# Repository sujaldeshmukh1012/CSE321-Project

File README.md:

<div id="top">

<!-- HEADER STYLE: CLASSIC -->
<div align="center">

# GuardianHAT

<em>Real-Time Embedded System for GPS Tracking and Environmental Monitoring</em>

<!-- BADGES -->

<em>Built with the tools and technologies:</em>

**C/C++ • ESP32-CAM • Arduino Nano • FreeRTOS • PlatformIO • KiCad PCB Design**

</div>
<br>

---

## Table of Contents

- [Overview](#overview)
- [Features](#features)
- [Hardware Components](#hardware-components)
- [PCB Design](#pcb-design)
  - [PCB Images](#pcb-images)
  - [Design Process](#design-process)
  - [Bill of Materials](#bill-of-materials)
- [Project Structure](#project-structure)
- [Getting Started](#getting-started)
  - [Prerequisites](#prerequisites)
  - [Installation](#installation)
  - [Usage](#usage)
  - [Testing](#testing)
- [System Architecture](#system-architecture)
- [Implimentation](#implimentation)
- [Contributing](#contributing)
- [License](#license)
- [Author](#author)
- [Acknowledgments](#acknowledgments)

---

## Overview

GuardianHAT is a comprehensive embedded systems solution that integrates GPS tracking, environmental sensing, and real-time monitoring capabilities. The project features two main components: an ESP32-CAM based system for camera functionality and location tracking, and an Arduino Nano RTOS implementation for sensor data processing with FreeRTOS task management.

The system includes a custom-designed PCB (Caretaker Board) that integrates all components for a professional, production-ready embedded solution.

**Key Highlights:**
- Real-time GPS satellite tracking and location monitoring
- Environmental sensing with MPU6050 (accelerometer/gyroscope)
- Distance measurement using VL53L0X ToF sensor
- OLED display (SSD1306) for real-time data visualization
- Custom PCB design with professional manufacturing files
- Multi-threaded RTOS implementation for concurrent task execution

---

## Features

### Core Functionality
- **GPS Tracking**: Real-time satellite position tracking with TinyGPS++ library
- **Motion Detection**: 6-axis motion sensing using MPU6050 (accelerometer + gyroscope)
- **Distance Measurement**: Precise ranging with VL53L0X Time-of-Flight sensor
- **Visual Display**: 128x64 OLED display for live sensor data and status information
- **Camera Module**: ESP32-CAM integration for image capture and processing
- **Real-Time OS**: FreeRTOS implementation for efficient task scheduling and resource management

### Technical Features
- Multi-tasking architecture with independent sensor polling tasks
- I2C and SPI communication protocols
- Low-power design optimizations
- Interrupt-driven button and buzzer control
- Hardware abstraction for easy sensor integration
- Professional PCB with proper power regulation and signal integrity

---

## Hardware Components

| Component | Model | Interface | Purpose |
|-----------|-------|-----------|---------|
| **Microcontroller** | ESP32-S3 (CAM) | - | Main processing unit with WiFi/BT |
| **Microcontroller** | Arduino Nano Every | - | RTOS sensor controller |
| **GPS Module** | NEO-6M | UART | Location tracking |
| **IMU Sensor** | MPU6050 | I2C | Motion and orientation |
| **Distance Sensor** | VL53L0X | I2C | Time-of-Flight ranging |
| **Display** | SSD1306 OLED | I2C | 128x64 visual feedback |
| **Camera** | OV2640 | - | Image capture |
| **Feedback** | Buzzer, LED| GPIO| User feedback|
| **Actuators** | Servos | PWM | Control |

---

## PCB Design

### PCB Images

The custom Caretaker PCB was designed in KiCad to integrate all system components on a single board.

<div style="display:flex;align-items:center;justify-content:space-between;" > 

</div>
<div style="display:flex;align-items:center;justify-content:space-between;" > 

</div>

### Design Process

**Tools Used:**
- **KiCad 6.0+**: Schematic capture and PCB layout
- **Component Libraries**: Custom footprints for Adafruit modules and sensors

**Manufacturing Files** (Generated Gerbers):
- `Caretaker-F_Cu.gbr` - Front copper layer
- `Caretaker-B_Cu.gbr` - Back copper layer
- `Caretaker-F_Mask.gbr` - Front soldermask
- `Caretaker-B_Mask.gbr` - Back soldermask
- `Caretaker-F_Paste.gbr` - Front paste layer (for stencil)
- `Caretaker-B_Paste.gbr` - Back paste layer
- `Caretaker-F_Silkscreen.gbr` - Front silkscreen
- `Caretaker-B_Silkscreen.gbr` - Back silkscreen
- `Caretaker-Edge_Cuts.gbr` - Board outline
- `Caretaker-job.gbrjob` - Gerber job file

**PCB Specifications:**
- **Layers**: 2-layer PCB
- **Dimensions**: 99mm x 70mm
- **Thickness**: 1.6mm (standard)
- **Copper Weight**: 1 oz (35 μm)
- **Surface Finish**: HASL

**Design Considerations:**
- Proper power plane separation for analog/digital circuits
- I2C pull-up resistors on SDA/SCL lines
- Decoupling capacitors near power pins
- Ground plane for noise reduction
- Clear component labeling on silkscreen

### Bill of Materials

Complete the quantities and part numbers based on your actual design:

| Qty | Value | Package | Description | Manufacturer Part # | Notes |
|-----|-------|---------|-------------|---------------------|-------|
| 1  | ESP32-S3 | Module | Main MCU with WiFi/BT | ESP32-S3-WROOM-1 | Seeed XIAO ESP32S3 |
| 1  | Arduino Nano | Module | RTOS Controller | ABX00028 | Arduino Nano Every |
| 1  | NEO-6M | Module | GPS Module | NEO-6M | U-blox GPS |
| 1  | MPU6050 | Module | 6-axis IMU | GY-521 | Accelerometer + Gyro |
| 1  | VL53L0X | Module | ToF Distance Sensor | - | Adafruit breakout |
| 1  | SSD1306 | Module | OLED Display | - | 128x64 I2C display |
| 1  | OV2640 | Module | Camera Module | - | ESP32-CAM compatible |
| 4  | Servo | SG90 | Micro Servo 9g | SG90 | Tower Pro |
| 1  | Buzzer | THT | Active/Passive Buzzer | - | 5V buzzer |
| 2 | LED | THT | Status Indicators | - | Red/Green |
| 2 | Resistor 4.7kΩ | THT | I2C Pull-up Resistors | - | 1% tolerance |
| 4 | Resistor 330Ω | THT | LED Current Limiting | - | - |
| 1 | Push Button | THT | User Input | 1825967-2 | Tactile switch |
| 4 | Capacitor 0.1µF | THT | Decoupling Capacitors | - | Ceramic, X7R |
| 2 | Capacitor 470µF | THT | Bulk Capacitors | - | Ceramic, X7R |
| 1 | Header | 2.54mm | UART/Debug | - | 4-pin header |
| 3 | Header | 2.54mm | I2C Expansion | - | 4-pin headers |

**Total Estimated Cost**: $50.00

**Suggested Suppliers:**
- DigiKey
- Mouser Electronics  
- Adafruit
- SparkFun
- Amazon (for modules)
- JLCPCB (for pcb fabrication)

---

## Project Structure

```sh
└── GuardianHAT/
    ├── ESP32_CAM/                    # ESP32-CAM module firmware
    │   ├── platformio.ini            # PlatformIO configuration
    │   ├── src/
    │   │   └── main.cpp              # Main ESP32 application
    │   ├── testing_code/             # Individual component tests
    │   │   ├── GPS.cpp               # GPS module testing
    │   │   ├── display.cpp           # OLED display testing
    │   │   └── buzzer_button_led.cpp # I/O peripheral tests
    │   └── lib/                      # External libraries
    │
    ├── NANO_RTOS/                    # Arduino Nano with FreeRTOS
    │   ├── platformio.ini            # PlatformIO configuration
    │   ├── src/
    │   │   └── main.cpp              # FreeRTOS task implementation
    │   └── lib/                      # RTOS and sensor libraries
    │
    ├── PCB_Design/                   # KiCad PCB project
    │   ├── Caretaker.kicad_pro       # KiCad project file
    │   ├── Caretaker.kicad_sch       # Schematic file
    │   ├── Caretaker.kicad_pcb       # PCB layout file
    │   ├── Library/                  # Custom component libraries
    │   │   ├── symbols/              # Custom schematic symbols
    │   │   └── footprints/           # Custom PCB footprints
    │   ├── Production/               # Manufacturing files (Gerbers)
    │      └── *.gbr                 # Gerber files for fab house
    │
    ├── LICENSE                       # Project license
    └── README.md                     # This file
```

---

## Getting Started

### Prerequisites

**Software Requirements:**
- **PlatformIO**: IDE extension for VS Code or CLI
- **Python 3.7+**: For PlatformIO installation
- **Git**: For version control
- **KiCad 7.0+**: For PCB design viewing/editing (optional)

**Hardware Requirements:**
- ESP32-S3 development board (Seeed XIAO ESP32S3 or similar)
- Arduino Nano Every
- USB-C cable for ESP32
- Micro-USB cable for Arduino Nano
- All sensors and components from BOM

### Installation

1. **Clone the repository:**

```sh
git clone https://github.com/sujaldeshmukh1012/GuardianHAT.git
cd GuardianHAT
```

2. **Install PlatformIO:**

```sh
# Install PlatformIO Core (CLI)
pip install platformio

# Or install VS Code + PlatformIO IDE extension
code --install-extension platformio.platformio-ide
```

3. **Install project dependencies:**

PlatformIO will automatically install dependencies defined in `platformio.ini` when you build the project.

```sh
# For ESP32-CAM module
cd ESP32_CAM
pio lib install

# For NANO RTOS module
cd ../NANO_RTOS
pio lib install
```

### Usage

**Build and Upload ESP32-CAM Firmware:**

```sh
cd ESP32_CAM
pio run --target upload
pio device monitor  # View serial output
```

**Build and Upload Arduino Nano Firmware:**

```sh
cd NANO_RTOS
pio run --target upload
pio device monitor  # View serial output
```

**Serial Monitor Settings:**
- Baud Rate: 115200
- Line Ending: Newline

**Expected Output:**
```
[GPS] Satellites: 8, Location: 42.9634° N, 78.7384° W
[MPU6050] Accel: X=0.02g Y=0.98g Z=0.05g
[VL53L0X] Distance: 245mm
[Display] Status: OK
```

### Testing

The project includes individual component test files in `ESP32_CAM/testing_code/`:

**Test GPS Module:**
```sh
# Edit platformio.ini to set src_dir to testing_code
# Then uncomment the GPS.cpp file
pio run --target upload
```

**Test Display:**
```sh
# Use display.cpp as main source
pio run --target upload
```

**Test I/O Peripherals:**
```sh
# Use buzzer_button_led.cpp as main source
pio run --target upload
```

**Run All Tests:**
```sh
# Both projects include test directories
cd NANO_RTOS
pio test

cd ../ESP32_CAM
pio test
```

---

## System Architecture

### ESP32-CAM Module
- **Main Tasks**: Camera capture, WiFi connectivity, GPS data logging
- **Sensors**: GPS (NEO-6M), Camera (OV2640)
- **Communication**: WiFi for data transmission

### Arduino Nano RTOS Module
- **Main Tasks**: Sensor polling, OLED display updates, real-time processing
- **RTOS Tasks**:
  - Task 1: MPU6050 data acquisition (100Hz)
  - Task 2: VL53L0X distance measurement (50Hz)
  - Task 3: Display update task (10Hz)
  - Task 4: User input handling (interrupt-based)
- **Communication**: I2C for sensors, SPI for potential expansions

### Communication Protocol
The two modules communicate via UART to share sensor data and coordinate actions.

---
## Implimentation

The project was designed and demoed for the CSE 321 class project at University at Buffalo.

I have used external power and step-down converters to provide ample power to the 5v and 3v3 systems.

**The class has a constraint to use from the shelf Arduino products like Nano, Uno, Mega. So the project used the full dev boards instead of a much compact custom board using only what is needed.**

<div style="display:flex;align-items:center;justify-content:space-between;" > 

</div>

<br>
<div style="display:flex;align-items:center;justify-content:center;">
  
</div>

---

## Author

<div align="center">

### Sujal Bhakare

**Systems Engineer | Computer Science Student**

</div>
---

## Acknowledgments

- **Adafruit Industries**: For excellent sensor libraries and breakout boards
- **Arduino Community**: For FreeRTOS port and examples
- **Espressif Systems**: For ESP32 development framework
- **KiCad EDA**: For open-source PCB design software
- **TinyGPS++**: Mikal Hart's GPS parsing library
- **Course Staff**: CSE321 instructor and TAs
- **My Amazing Teammate:** Andrew Collado [LinkedIn](https://www.linkedin.com/in/andrew-collado/)

### References
- [ESP32-CAM Documentation](https://docs.espressif.com/)
- [FreeRTOS Documentation](https://www.freertos.org/Documentation/RTOS_book.html)
- [KiCad Documentation](https://docs.kicad.org/)
- [PlatformIO Documentation](https://docs.platformio.org/)

---

<div align="center">

**[⬆ Back to Top](#top)**

Made with ❤️ by [Andrew Collado]((https://www.linkedin.com/in/andrew-collado/)) & [Sujal Bhakare](https://sujalbhakare.com)

</div>

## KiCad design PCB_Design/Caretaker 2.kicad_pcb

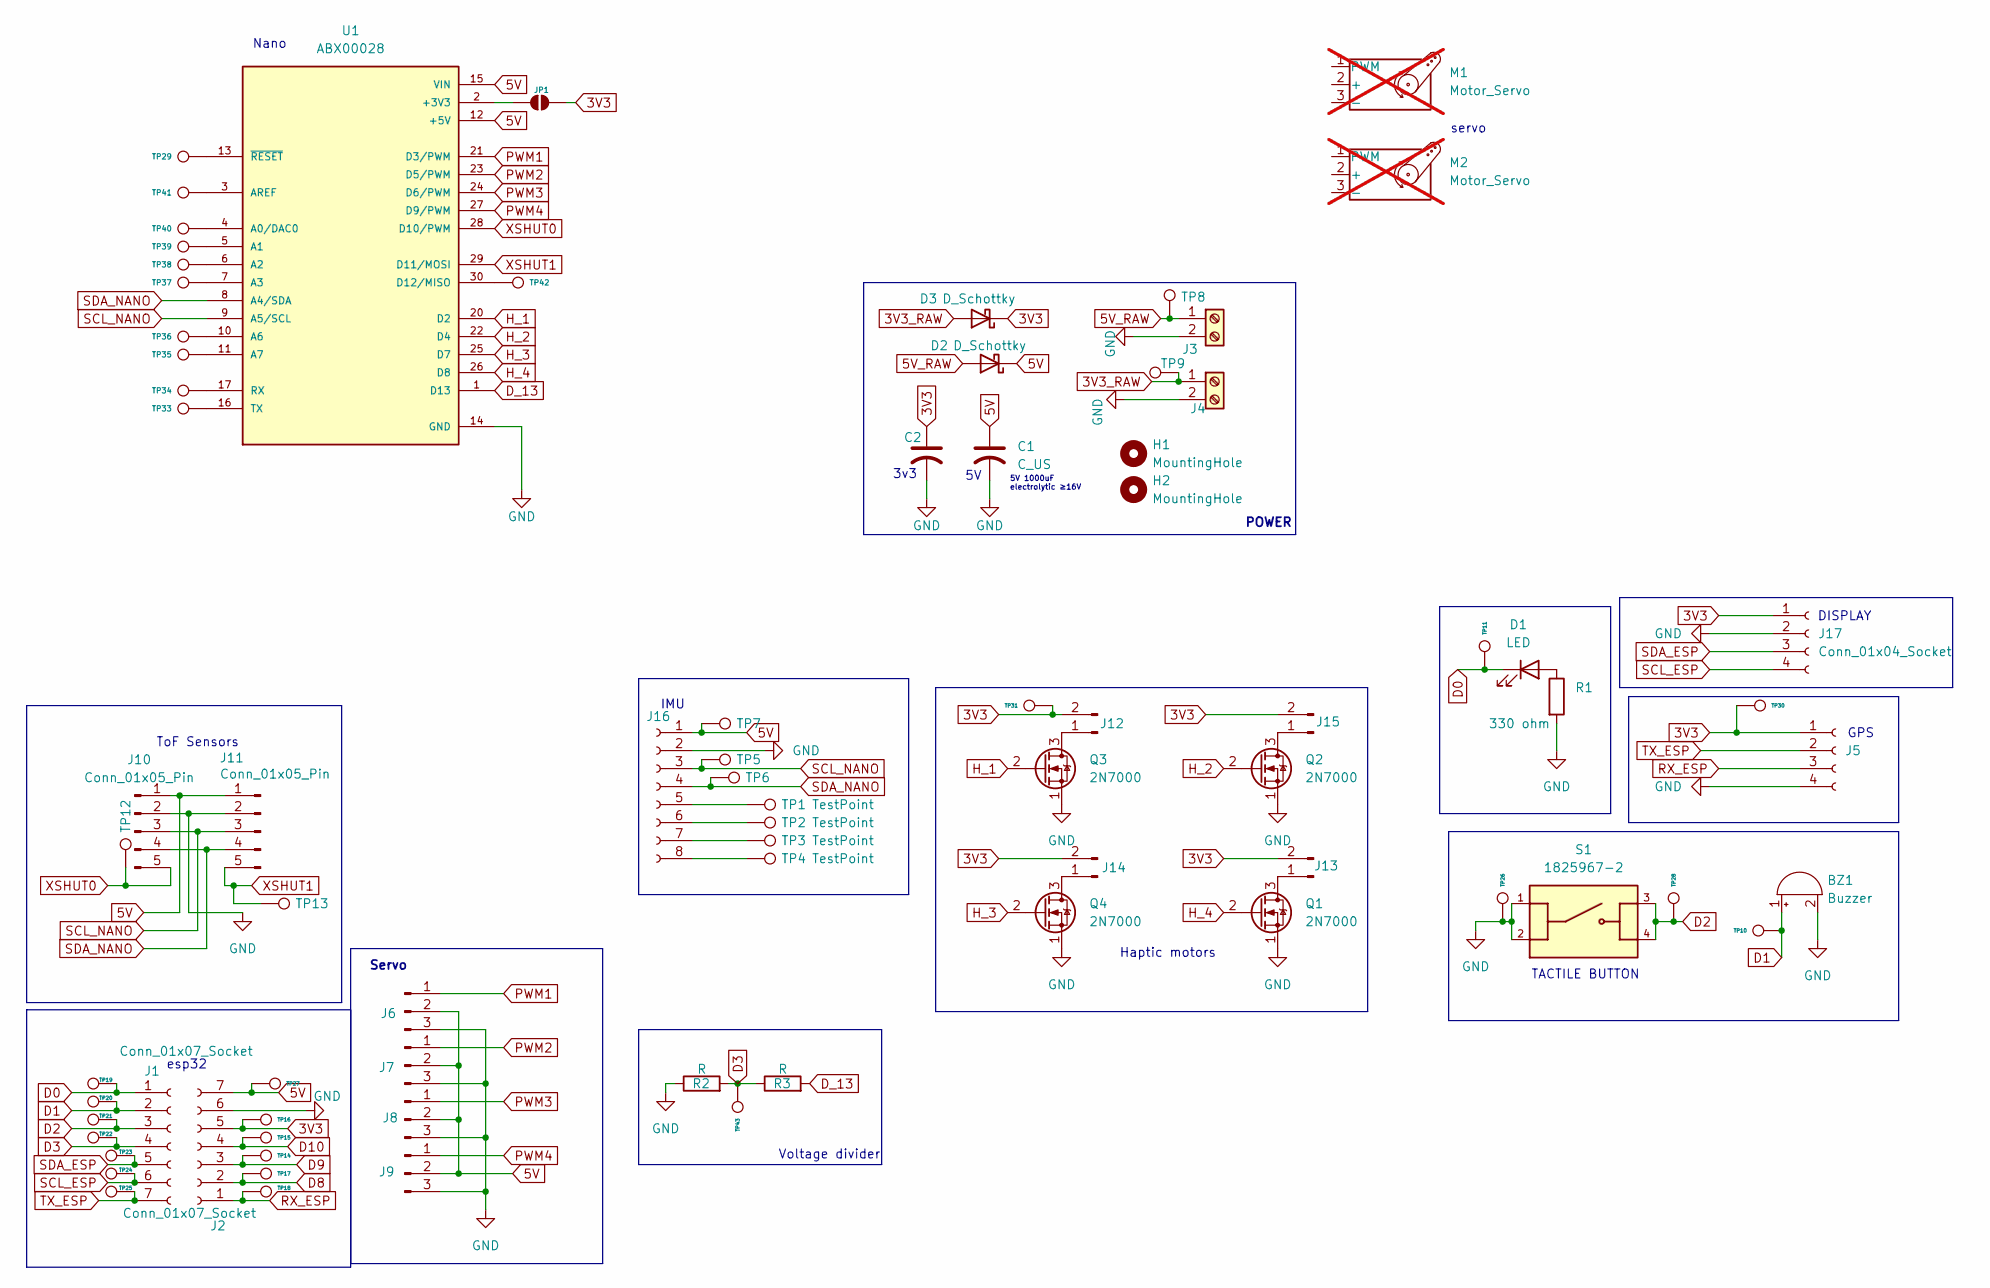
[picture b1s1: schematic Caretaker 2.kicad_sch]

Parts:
BZ1: Buzzer; Buzzer_12x9.5RM7.6
C1: C_US; C_Radial_D6.3mm_H5.0mm_P2.50mm
C2: C_US; C_Radial_D6.3mm_H11.0mm_P2.50mm
D1: LED; LED_D5.0mm
D2, D3: D_Schottky; D_5W_P5.08mm_Vertical_KathodeUp
H1, H2: MountingHole; MountingHole_2.7mm_M2.5
J1, J2: Conn_01x07_Socket; PinHeader_1x07_P2.54mm_Vertical
J3, J4: Screw_Terminal_01x02; TerminalBlock_MaiXu_MX126-5.0-02P_1x02_P5.00mm
J5, J17: Conn_01x04_Socket; PinHeader_1x04_P2.54mm_Vertical
J6, J7, J8, J9: Conn_01x03_Pin; PinHeader_1x03_P2.54mm_Vertical
J10, J11: Conn_01x05_Pin; PinHeader_1x05_P2.54mm_Vertical
J12, J13, J14, J15: Conn_01x02_Pin; PinHeader_1x02_P2.54mm_Vertical
J16: Conn_01x08_Socket; PinHeader_1x08_P2.54mm_Vertical
JP1: SolderJumper_2_Open; SolderJumper-2_P1.3mm_Open_RoundedPad1.0x1.5mm
M1, M2: Motor_Servo; MountingHole_8.4mm_M8_Pad_TopOnly; not fitted
Q1, Q2, Q3, Q4: 2N7000; TO-92_Inline
R1: 330 ohm; R_Axial_DIN0204_L3.6mm_D1.6mm_P5.08mm_Horizontal
R2, R3: R; R_Axial_DIN0204_L3.6mm_D1.6mm_P2.54mm_Vertical
S1: 1825967-2; SW_1825967-2
TP1, TP2, TP3, TP4, TP5, TP6, TP7, TP8, TP9, TP10, TP11, TP12, TP13, TP14, TP15, TP16, TP17, TP18, TP19, TP20, TP21, TP22, TP23, TP24, TP25, TP26, TP27, TP28, TP29, TP30, TP31, TP33, TP34, TP35, TP36, TP37, TP38, TP39, TP40, TP41, TP42, TP43: TestPoint; TestPoint_Pad_1.0x1.0mm
U1: ABX00028; MODULE_ABX00028; PARTREV 6-11-19

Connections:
3V3: C2.1, D3.1 (K), J2.5, J5.1, J12.2, J13.2, J14.2, J15.2, J17.1, JP1.2 (B), TP16.1, TP30.1, TP31.1
3V3_RAW: D3.2 (A), J4.1, TP9.1
5V: C1.1, D2.1 (K), J2.7, J6.2, J7.2, J8.2, J9.2, J10.1, J11.1, J16.1, TP7.1, TP27.1, U1.12 (+5V), U1.15 (VIN)
5V_RAW: D2.2 (A), J3.1, TP8.1
D0: D1.1 (K), J1.1, TP11.1, TP19.1
D1: BZ1.1 (+), J1.2, TP10.1, TP20.1
D2: J1.3, S1.3, S1.4, TP21.1, TP28.1
D3: J1.4, R2.2, R3.1, TP22.1, TP43.1
D8: J2.2, TP17.1
D9: J2.3, TP14.1
D10: J2.4, TP15.1
D_13: R3.2, U1.1 (D13)
GND: BZ1.2 (-), C1.2, C2.2, J2.6, J3.2, J4.2, J5.4, J6.3, J7.3, J8.3, J9.3, J10.2, J11.2, J16.2, J17.2, Q1.1 (S), Q2.1 (S), Q3.1 (S), Q4.1 (S), R1.2, R2.1, S1.1, S1.2, TP26.1, U1.14 (GND), U1.19 (GND)
H_1: Q3.2 (G), U1.20 (D2)
H_2: Q2.2 (G), U1.22 (D4)
H_3: Q4.2 (G), U1.25 (D7)
H_4: Q1.2 (G), U1.26 (D8)
unnamed: D1.2 (A), R1.1
unnamed: J12.1, Q3.3 (D)
unnamed: J13.1, Q1.3 (D)
unnamed: J14.1, Q4.3 (D)
unnamed: J15.1, Q2.3 (D)
unnamed: J16.5, TP1.1
unnamed: J16.6, TP2.1
unnamed: J16.7, TP3.1
unnamed: J16.8, TP4.1
unnamed: JP1.1 (A), U1.2 (+3V3)
unnamed: TP29.1, U1.13 (~RESET), U1.18 (~RESET)
unnamed: TP40.1, U1.4 (A0/DAC0)
unnamed: TP39.1, U1.5 (A1)
unnamed: TP38.1, U1.6 (A2)
unnamed: TP37.1, U1.7 (A3)
unnamed: TP36.1, U1.10 (A6)
unnamed: TP35.1, U1.11 (A7)
unnamed: TP41.1, U1.3 (AREF)
unnamed: TP42.1, U1.30 (D12/MISO)
unnamed: TP34.1, U1.17 (RX)
unnamed: TP33.1, U1.16 (TX)
PWM1: J6.1, U1.21 (D3/PWM)
PWM2: J7.1, U1.23 (D5/PWM)
PWM3: J8.1, U1.24 (D6/PWM)
PWM4: J9.1, U1.27 (D9/PWM)
RX_ESP: J2.1, J5.3, TP18.1
SCL_ESP: J1.6, J17.4, TP24.1
SCL_NANO: J10.3, J11.3, J16.3, TP5.1, U1.9 (A5/SCL)
SDA_ESP: J1.5, J17.3, TP23.1
SDA_NANO: J10.4, J11.4, J16.4, TP6.1, U1.8 (A4/SDA)
TX_ESP: J1.7, J5.2, TP25.1
XSHUT0: J10.5, TP12.1, U1.28 (D10/PWM)
XSHUT1: J11.5, TP13.1, U1.29 (D11/MOSI)

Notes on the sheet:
ToF Sensors
GPS
DISPLAY
POWER
TACTILE BUTTON
Nano
Haptic motors
esp32
Servo
servo
5V 1000uF electrolytic ≥16V
3v3
Voltage divider
IMU

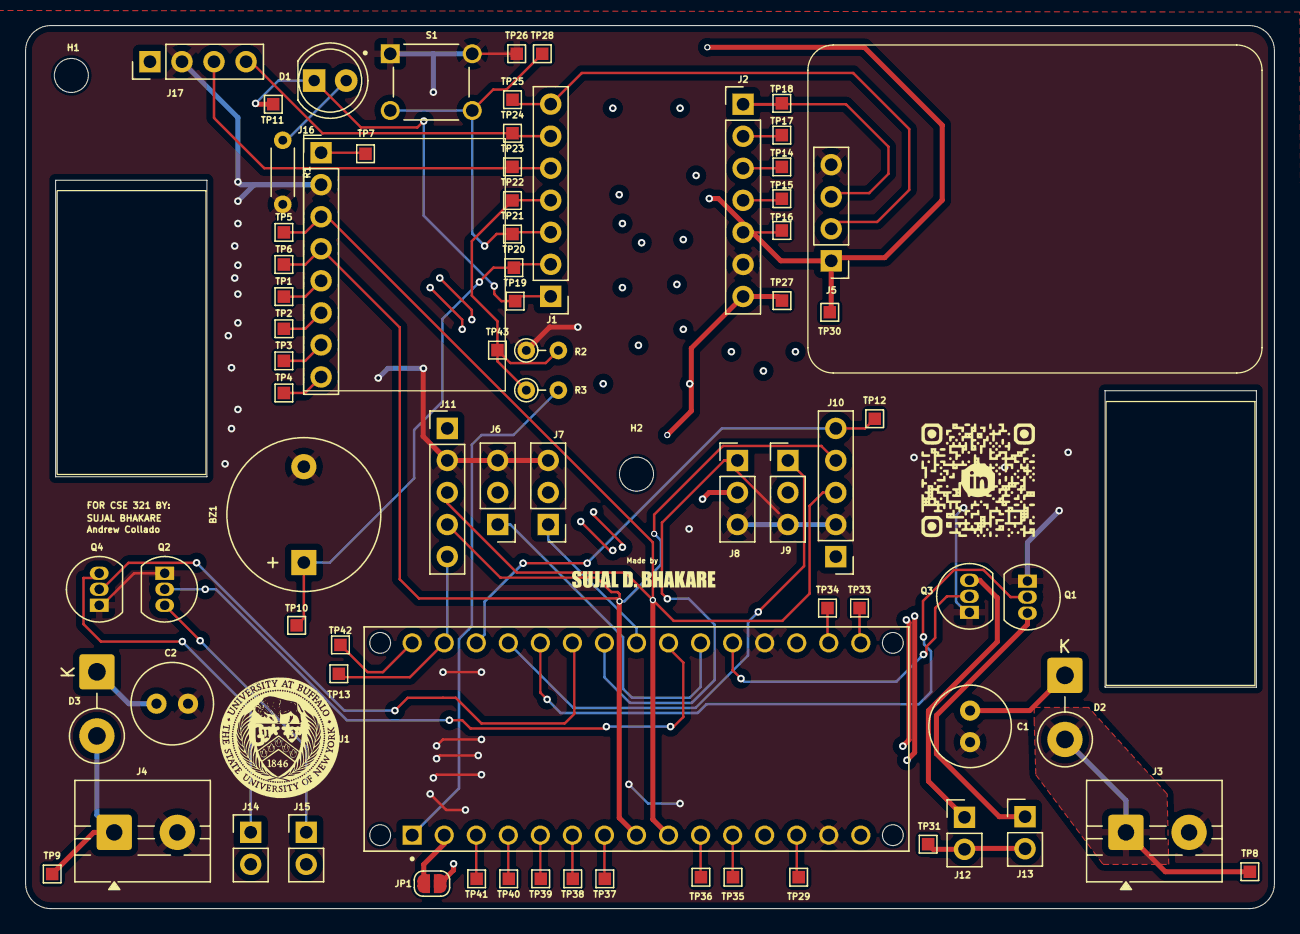
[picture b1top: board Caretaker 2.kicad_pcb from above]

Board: 2 copper layers, 99.0 x 70.0 mm, 79 parts (0 on the bottom side), 50 nets.

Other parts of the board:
M1#2: Motor_Servo; MountingHole_8.4mm_M8_Pad_TopOnly

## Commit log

2025-10-17 Add initial content to README.md
2025-10-17 Platform .ini Poject Setup
2025-10-17 Platformusage info added in README
2025-10-17 Platform usage info added in README
2025-10-17 README Fixed
2025-11-02 ESP32-CAM Code added
2025-11-02 Restructured the folders
2025-11-06 ESP32 Cam code working added
2025-11-06 ESP32 cam working code added finally
2025-11-06 Stop tracking folder and add to .gitignore
2025-11-11 Nano Servo Code
2025-11-11 Drat of main code
2025-11-11 Removed GPS, Extra code from Nano
2025-11-22 phase 2 code
2025-12-07 Update README with GuardianHat branding and add schematics PDF
2025-12-07 README.md updated
2025-12-08 README.md changes
2025-12-08 README.md video added
2025-12-08 README.md video updated
2025-12-08 README.md text updated
2025-12-08 badge added
